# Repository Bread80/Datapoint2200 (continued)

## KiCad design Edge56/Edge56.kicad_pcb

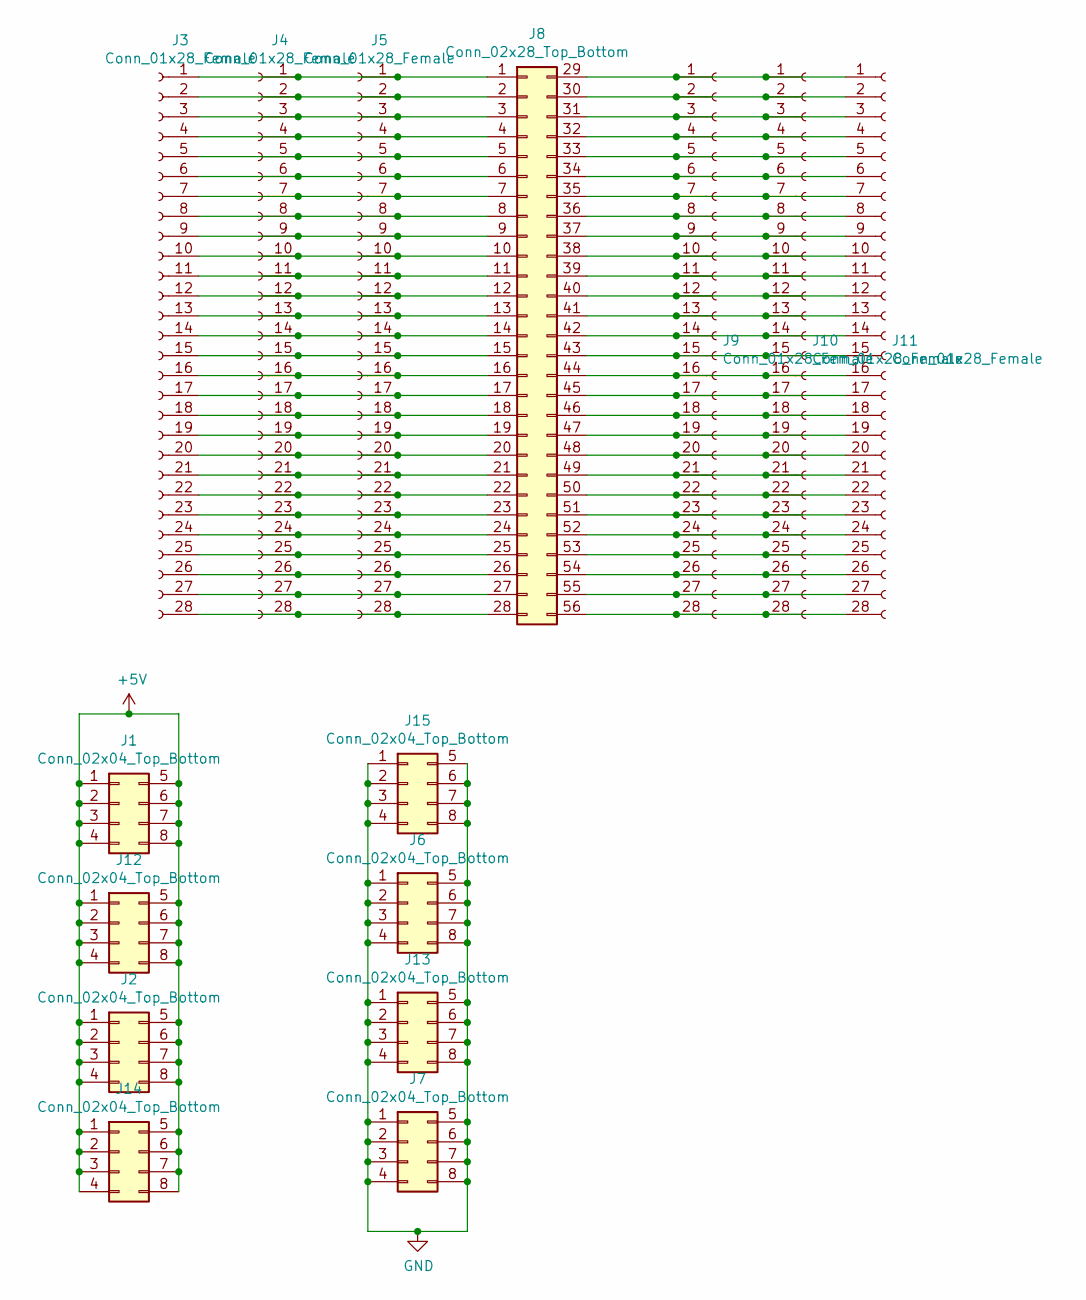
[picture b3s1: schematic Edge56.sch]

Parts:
J1, J6: Conn_02x04_Top_Bottom; PinHeader_2x04_P2.54mm_Horizontal
J2, J7, J12, J13: Conn_02x04_Top_Bottom; PinSocket_2x04_P2.54mm_Horizontal
J3, J4, J5, J9, J10, J11: Conn_01x28_Female; PinSocket_1x28_P2.54mm_Vertical
J8: Conn_02x28_Top_Bottom; EdgeConn_Socket_56_Pin_Pitch_3.96mm
J14, J15: Conn_02x04_Top_Bottom; PinHeader_2x04_P2.54mm_Vertical

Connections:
+5V: J1.1, J1.2, J1.3, J1.4, J1.5, J1.6, J1.7, J1.8, J2.1, J2.2, J2.3, J2.4, J2.5, J2.6, J2.7, J2.8, J12.1, J12.2, J12.3, J12.4, J12.5, J12.6, J12.7, J12.8, J14.1, J14.2, J14.3, J14.4, J14.5, J14.6, J14.7, J14.8
GND: J6.1, J6.2, J6.3, J6.4, J6.5, J6.6, J6.7, J6.8, J7.1, J7.2, J7.3, J7.4, J7.5, J7.6, J7.7, J7.8, J13.1, J13.2, J13.3, J13.4, J13.5, J13.6, J13.7, J13.8, J15.1, J15.2, J15.3, J15.4, J15.5, J15.6, J15.7, J15.8
unnamed: J3.1, J4.1, J5.1, J8.1
unnamed: J3.2, J4.2, J5.2, J8.2
unnamed: J3.3, J4.3, J5.3, J8.3
unnamed: J3.4, J4.4, J5.4, J8.4
unnamed: J3.5, J4.5, J5.5, J8.5
unnamed: J3.6, J4.6, J5.6, J8.6
unnamed: J3.7, J4.7, J5.7, J8.7
unnamed: J3.8, J4.8, J5.8, J8.8
unnamed: J3.9, J4.9, J5.9, J8.9
unnamed: J3.10, J4.10, J5.10, J8.10
unnamed: J3.11, J4.11, J5.11, J8.11
unnamed: J3.12, J4.12, J5.12, J8.12
unnamed: J3.13, J4.13, J5.13, J8.13
unnamed: J3.14, J4.14, J5.14, J8.14
unnamed: J3.15, J4.15, J5.15, J8.15
unnamed: J3.16, J4.16, J5.16, J8.16
unnamed: J3.17, J4.17, J5.17, J8.17
unnamed: J3.18, J4.18, J5.18, J8.18
unnamed: J3.19, J4.19, J5.19, J8.19
unnamed: J3.20, J4.20, J5.20, J8.20
unnamed: J3.21, J4.21, J5.21, J8.21
unnamed: J3.22, J4.22, J5.22, J8.22
unnamed: J3.23, J4.23, J5.23, J8.23
unnamed: J3.24, J4.24, J5.24, J8.24
unnamed: J3.25, J4.25, J5.25, J8.25
unnamed: J3.26, J4.26, J5.26, J8.26
unnamed: J3.27, J4.27, J5.27, J8.27
unnamed: J3.28, J4.28, J5.28, J8.28
unnamed: J8.29, J9.1, J10.1, J11.1
unnamed: J8.30, J9.2, J10.2, J11.2
unnamed: J8.31, J9.3, J10.3, J11.3
unnamed: J8.32, J9.4, J10.4, J11.4
unnamed: J8.33, J9.5, J10.5, J11.5
unnamed: J8.34, J9.6, J10.6, J11.6
unnamed: J8.35, J9.7, J10.7, J11.7
unnamed: J8.36, J9.8, J10.8, J11.8
unnamed: J8.37, J9.9, J10.9, J11.9
unnamed: J8.38, J9.10, J10.10, J11.10
unnamed: J8.39, J9.11, J10.11, J11.11
unnamed: J8.40, J9.12, J10.12, J11.12
unnamed: J8.41, J9.13, J10.13, J11.13
unnamed: J8.42, J9.14, J10.14, J11.14
unnamed: J8.43, J9.15, J10.15, J11.15
unnamed: J8.44, J9.16, J10.16, J11.16
unnamed: J8.45, J9.17, J10.17, J11.17
unnamed: J8.46, J9.18, J10.18, J11.18
unnamed: J8.47, J9.19, J10.19, J11.19
unnamed: J8.48, J9.20, J10.20, J11.20
unnamed: J8.49, J9.21, J10.21, J11.21
unnamed: J8.50, J9.22, J10.22, J11.22
unnamed: J8.51, J9.23, J10.23, J11.23
unnamed: J8.52, J9.24, J10.24, J11.24
unnamed: J8.53, J9.25, J10.25, J11.25
unnamed: J8.54, J9.26, J10.26, J11.26
unnamed: J8.55, J9.27, J10.27, J11.27
unnamed: J8.56, J9.28, J10.28, J11.28

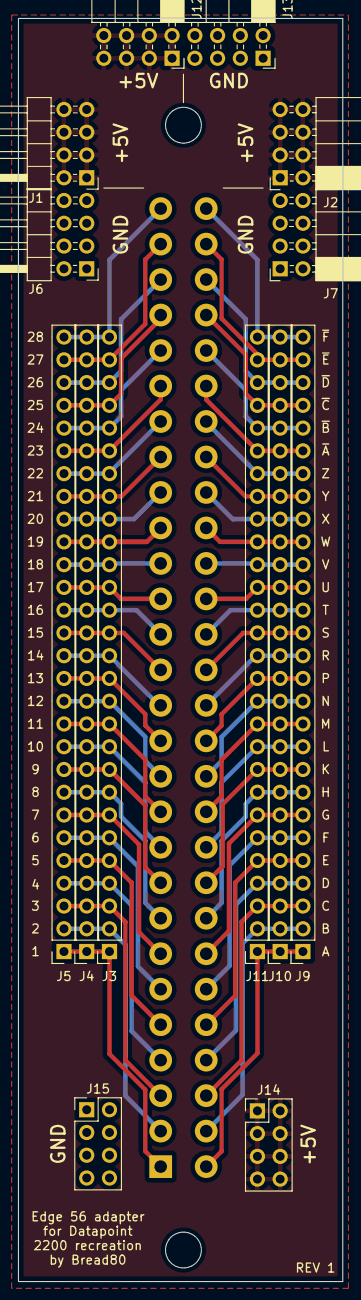
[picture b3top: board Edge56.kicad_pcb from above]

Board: 2 copper layers, 36.2 x 141.0 mm, 15 parts (1 on the bottom side), 58 nets.

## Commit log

2022-06-19 Initialise
2022-06-19 README update
    Better formatting and extra board detail
2023-04-07 Decoder 1 Rev 1
2024-10-31 Schematics for display & keyboard, adding LEDs to processor PCB
2024-11-01 Added Decoder PCB photos
2024-11-01 Fix image link
2024-11-01 Added Memory PCB photos
2024-11-01 Added renders of processor PCB
